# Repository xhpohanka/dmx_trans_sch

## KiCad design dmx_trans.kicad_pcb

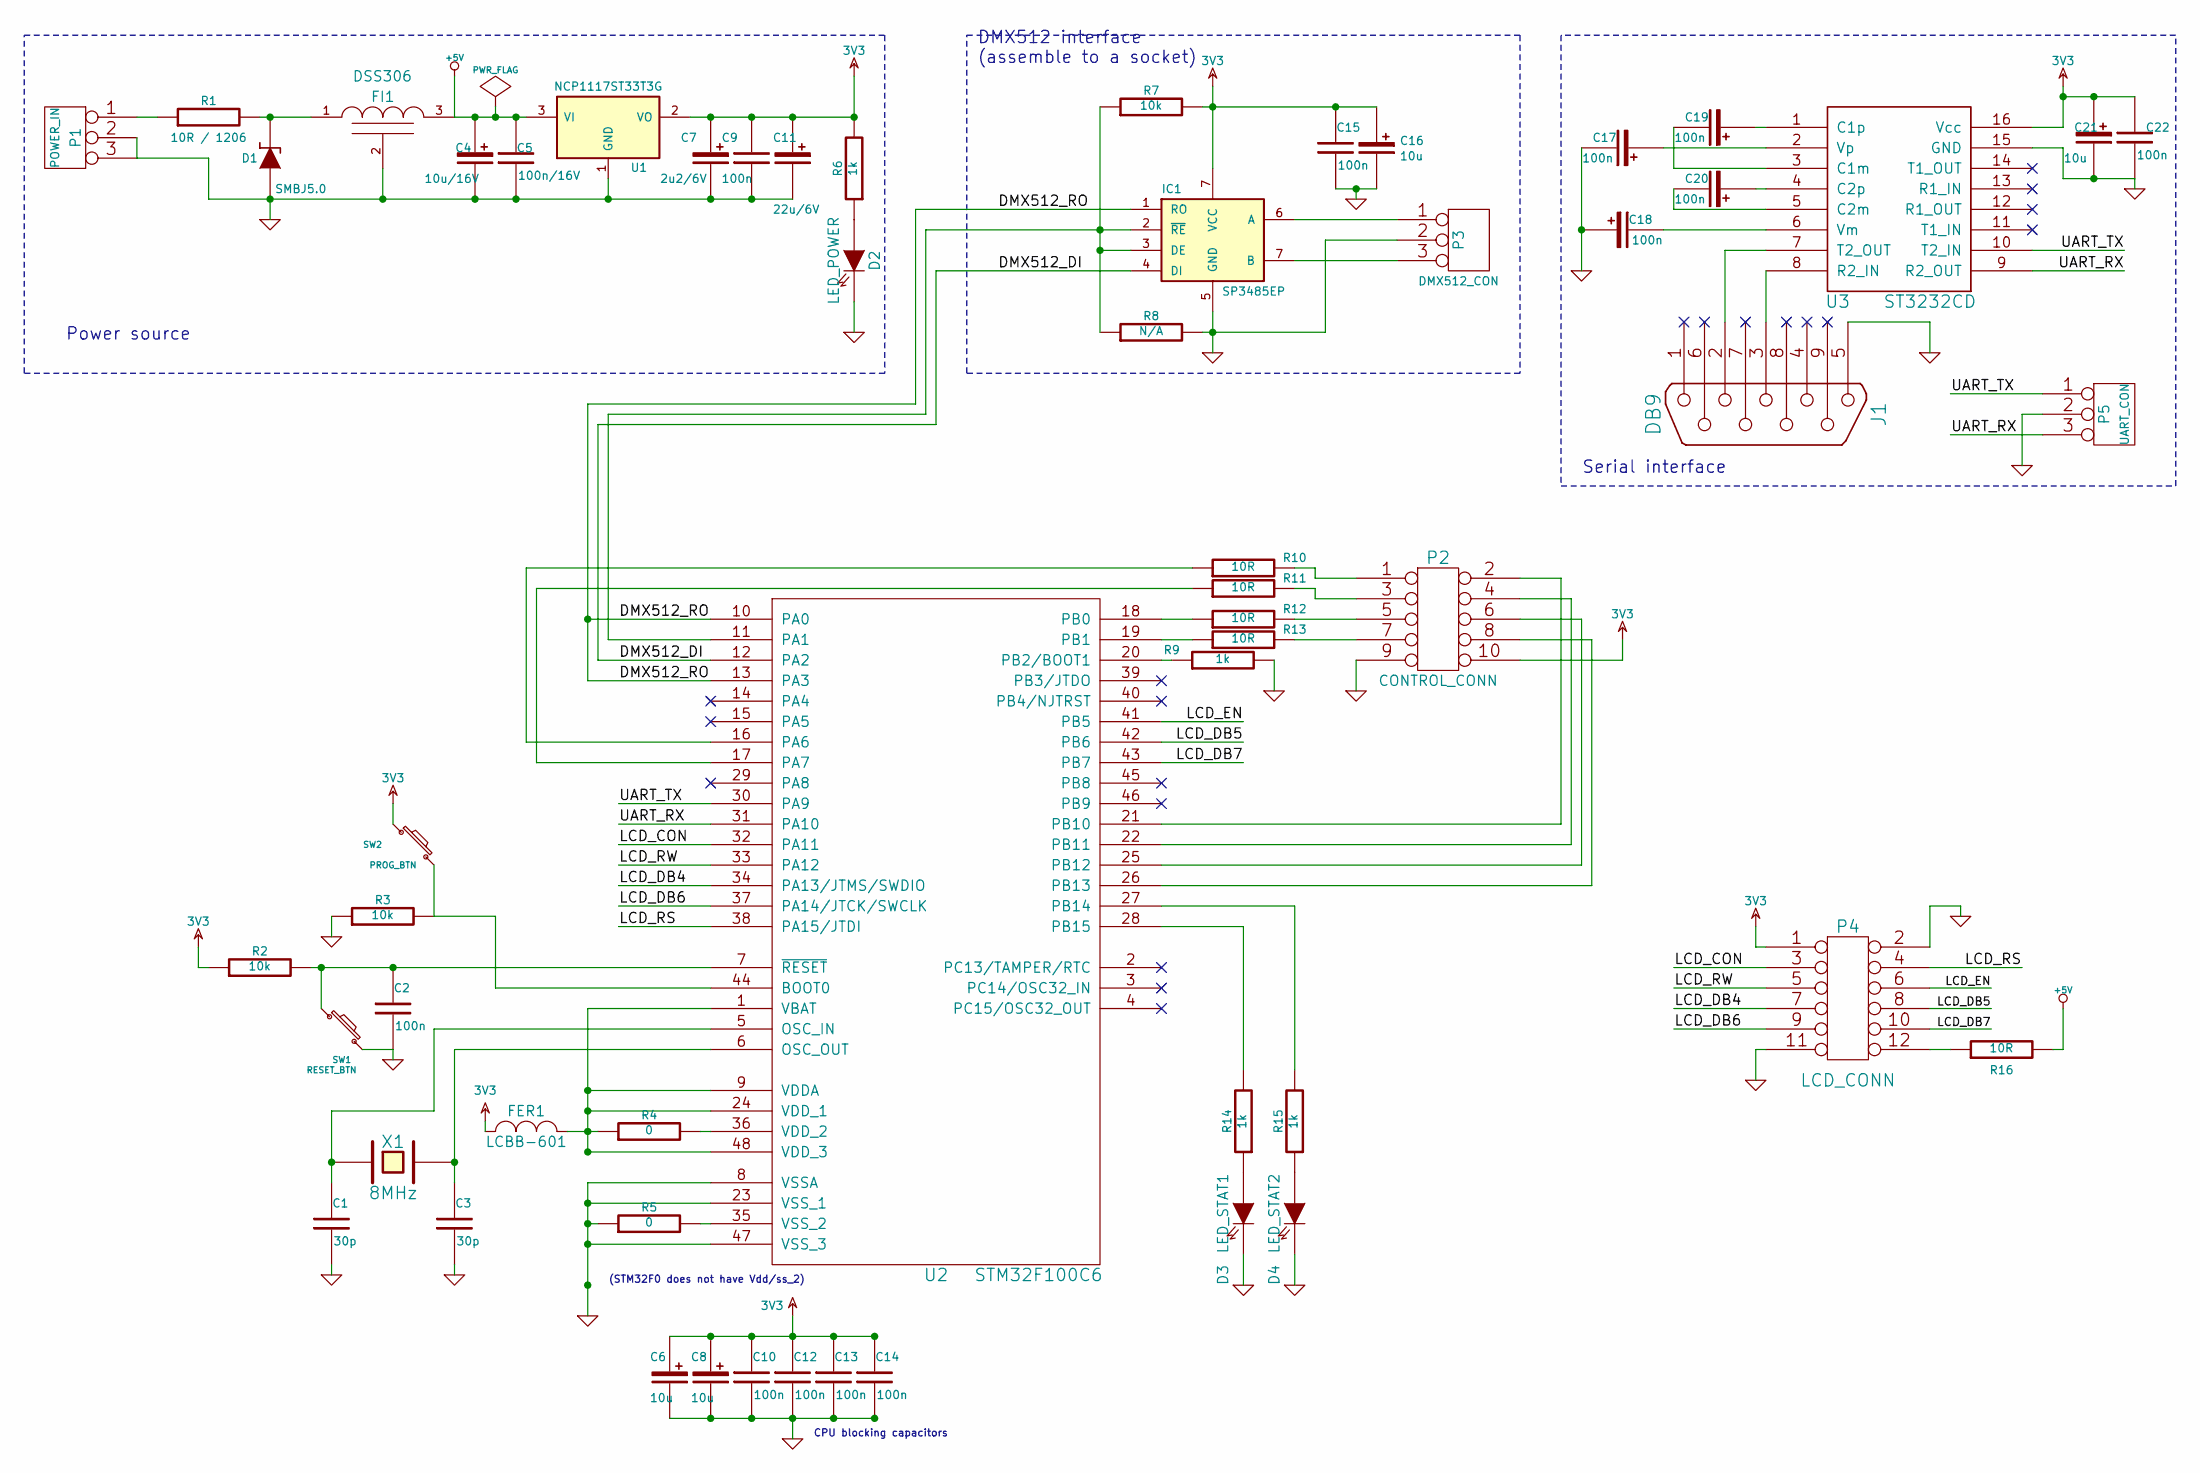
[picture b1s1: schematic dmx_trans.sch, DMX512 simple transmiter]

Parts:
C1, C3: 30p; c_0805
C2, C9, C10, C12, C13, C14, C15, C17, C18, C19, C20, C22: 100n; c_0805
C4: 10u/16V; c_tant_A
C5: 100n/16V; c_tant_A
C6, C8, C16, C21: 10u; c_tant_A
C7: 2u2/6V; c_tant_A
C11: 22u/6V; c_tant_A
D1: SMBJ5.0; DO-214AA(SMB)
D2: LED_POWER; LED-0805
D3: LED_STAT1; LED-0805
D4: LED_STAT2; LED-0805
FER1: LCBB-601; SM0805
FI1: DSS306; DSS6
IC1: SP3485EP; DIP-8__300
J1: DB9; DB9M_CI
P1: POWER_IN; BARREL_JACK
P2: CONTROL_CONN; PIN_ARRAY_5x2
P3: DMX512_CON; PINHEAD1-3
P4: LCD_CONN; pin_array_6x2
P5: UART_CON; PIN_ARRAY_3X1
R1: 10R / 1206; SM1206
R2, R3, R7: 10k; SM0805
R4, R5: 0; SM0805
R6, R9, R14, R15: 1k; SM0805
R8: N/A; SM0805
R10, R11, R12, R13, R16: 10R; SM0805
SW1: RESET_BTN; switch-tact-DTSM-3
SW2: PROG_BTN; switch-tact-DTSM-3
U1: NCP1117ST33T3G; DPAK2
U2: STM32F100C6; LQFP48
U3: ST3232CD; SO16N
X1: 8MHz; HC-18UV

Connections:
+5V: C4.1, C5.1, FI1.3 (VO), R16.2, U1.3 (VI)
/DMX512_DI: IC1.4 (DI), U2.12 (PA2)
/DMX512_RO: IC1.1 (RO), U2.10 (PA0), U2.13 (PA3)
/LCD_CON: P4.3, U2.32 (PA11)
/LCD_DB4: P4.7, U2.34 (PA13/JTMS/SWDIO)
/LCD_DB5: P4.8, U2.42 (PB6)
/LCD_DB6: P4.9, U2.37 (PA14/JTCK/SWCLK)
/LCD_DB7: P4.10, U2.43 (PB7)
/LCD_EN: P4.6, U2.41 (PB5)
/LCD_RS: P4.4, U2.38 (PA15/JTDI)
/LCD_RW: P4.5, U2.33 (PA12)
/UART_RX: P5.3, U2.31 (PA10), U3.9 (R2_OUT)
/UART_TX: P5.1, U2.30 (PA9), U3.10 (T2_IN)
GND: C1.2, C2.2, C3.2, C4.2, C5.2, C6.2, C7.2, C8.2, C9.2, C10.2, C11.2, C12.2, C13.2, C14.2, C15.2, C16.2, C17.2, C18.1, C21.2, C22.2, D1.1 (A), D2.2 (K), D3.2 (K), D4.2 (K), FI1.2 (GND), IC1.5 (GND), J1.5, P1.2 (PM), P1.3, P2.9, P3.2 (PM), P4.2, P4.11, P5.2 (PM), R3.1, R5.1, R8.2, R9.2, SW1.2, U1.1 (GND), U2.8 (VSSA), U2.23 (VSS_1), U2.47 (VSS_3), U3.15 (GND)
unnamed: R15.2, U2.27 (PB14)
unnamed: R14.2, U2.28 (PB15)
unnamed: D3.1 (A), R14.1
unnamed: D4.1 (A), R15.1
unnamed: C3.1, U2.6 (OSC_OUT), X1.2
unnamed: R9.1, U2.20 (PB2/BOOT1)
unnamed: R5.2, U2.35 (VSS_2)
unnamed: R4.2, U2.36 (VDD_2)
unnamed: C1.1, U2.5 (OSC_IN), X1.1
unnamed: C17.1, U3.2 (Vp)
unnamed: C18.2, U3.6 (Vm)
unnamed: C19.2, U3.3 (C1m)
unnamed: C19.1, U3.1 (C1p)
unnamed: C20.1, U3.4 (C2p)
unnamed: C20.2, U3.5 (C2m)
unnamed: J1.2, U3.7 (T2_OUT)
unnamed: J1.3, U3.8 (R2_IN)
unnamed: P4.12, R16.1
unnamed: P1.1, R1.1
unnamed: P2.7, R13.2
unnamed: P2.5, R12.2
unnamed: R11.1, U2.17 (PA7)
unnamed: P2.3, R11.2
unnamed: R10.1, U2.16 (PA6)
unnamed: P2.1, R10.2
unnamed: R12.1, U2.18 (PB0)
unnamed: R13.1, U2.19 (PB1)
unnamed: P2.8, U2.26 (PB13)
unnamed: P2.2, U2.21 (PB10)
unnamed: P2.4, U2.22 (PB11)
unnamed: P2.6, U2.25 (PB12)
unnamed: R3.2, SW2.2, U2.44 (BOOT0)
unnamed: IC1.6 (A), P3.1
unnamed: D2.1 (A), R6.1
unnamed: D1.2 (K), FI1.1 (VI), R1.2
unnamed: C2.1, R2.2, SW1.1, U2.7 (~RESET)
unnamed: IC1.2 (~RE~), IC1.3 (DE), R7.1, R8.1, U2.11 (PA1)
unnamed: FER1.2, R4.1, U2.1 (VBAT), U2.9 (VDDA), U2.24 (VDD_1), U2.48 (VDD_3)

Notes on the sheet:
Power source
DMX512 interface (assemble to a socket)
Serial interface
(STM32F0 does not have Vdd/ss_2)
CPU blocking capacitors

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
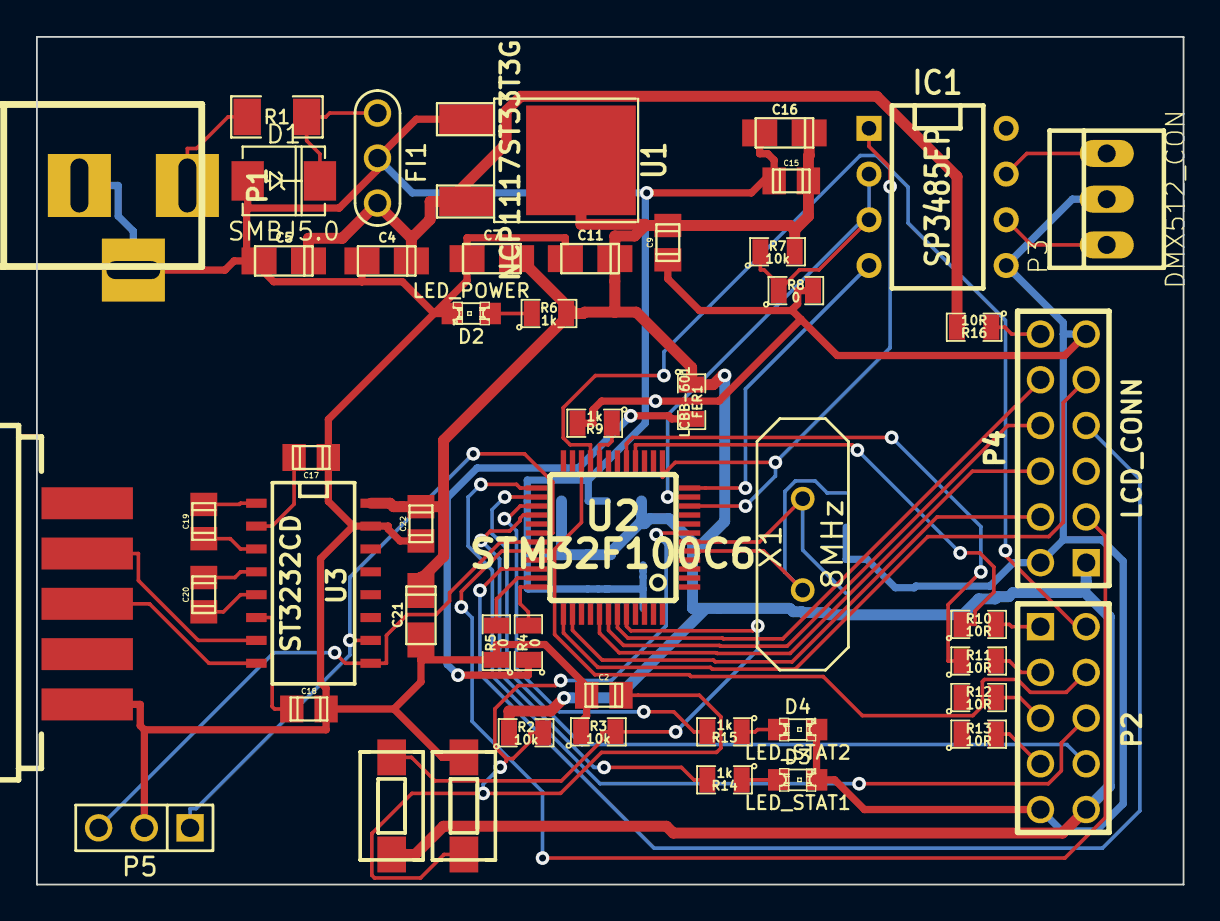
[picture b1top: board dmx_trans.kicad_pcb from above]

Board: 2 copper layers, 63.7 x 47.1 mm, 57 parts (0 on the bottom side), 54 nets.

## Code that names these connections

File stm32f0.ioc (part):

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Mcu.Name=STM32F051C6Tx
Mcu.Package=LQFP48
PA0.Mode=PWM-Input-1
PA0.Signal=TIM2_CH1_ETR
PA1.Signal=GPIO_Output
PA10.Mode=Asynchronous
PA10.Signal=USART1_RX
PA2.Mode=Asynchronous
PA2.Signal=USART2_TX
PA3.Mode=Asynchronous
PA3.Signal=USART2_RX
PA6.Mode=IN6
PA6.Signal=ADC_IN6
PA7.Mode=IN7
PA7.Signal=ADC_IN7
PA9.Mode=Asynchronous
PA9.Signal=USART1_TX
PB0.Mode=IN8
PB0.Signal=ADC_IN8
PB1.Mode=IN9
PB1.Signal=ADC_IN9
PB14.Signal=GPIO_Output
PB15.Signal=GPIO_Output

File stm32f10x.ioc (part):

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Mcu.Name=STM32F101C(4-6)Tx
Mcu.Package=LQFP48
PA10.Mode=Asynchronous
PA10.Signal=USART1_RX
PA13.Mode=JTAG(5-pin)
PA13.Signal=SYS_JTMS-SWDIO
PA14.Mode=JTAG(5-pin)
PA14.Signal=SYS_JTCK-SWCLK
PA15.Mode=JTAG(5-pin)
PA15.Signal=SYS_JTDI
PA2.Mode=Asynchronous
PA2.Signal=USART2_TX
PA3.Mode=Asynchronous
PA3.Signal=USART2_RX
PA9.Mode=Asynchronous
PA9.Signal=USART1_TX
PB3.Mode=JTAG(5-pin)
PB3.Signal=SYS_JTDO-TRACESWO
PB4.Mode=JTAG(5-pin)
PB4.Signal=SYS_JTRST

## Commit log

2013-05-18 Initial commit
    - finished schematics
2013-05-18 Schematics updated
    - filled values
    - filled title block
    - connector fixes
2013-05-22 Start of routing
    - footprints assigned
    - initial part placement
